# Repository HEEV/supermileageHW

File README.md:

# Cedarville Supermileage HW
Kicad files for PCBs on the Ceaderville Supermileage team. Also includes wiring diagrams and schematics
drawn in Kicad.
#Contents of Folders
* Library Folders
    * EllicottSamuel: Files I made before supermileage which were too much work to port over.
    *  parts_library: Files dedicated for the supermileage team.

* Project Folders
    * can_sensor: PCB to connect generic sensors to the CANBus.
    * current_sensor: Three port current sensor board that connects to the CANBus. 
	Current sensor chip is the Allegro ACS710.
    * pressure_sensor: Pressure sensor board, output as an analog voltage. 
	Supported sensors are the Honeywell ASDX100A24R, Honeywell HSCDRR004MD, and the
	AllSensors G4V-Mini.
    * Sting: wiring diagrams and schematics for Sting produced using Kicad.
        * wiring diagrams: kicad files for the wiring diagrams.
        * schematics: kicad files for the schematics.
    * Urbie: wiring diagrams and schematics for Urbie produced using Kicad.
    	* wiring diagrams: kicad files for the wiring diagrams.
        * schematics: kicad files for the schematics.

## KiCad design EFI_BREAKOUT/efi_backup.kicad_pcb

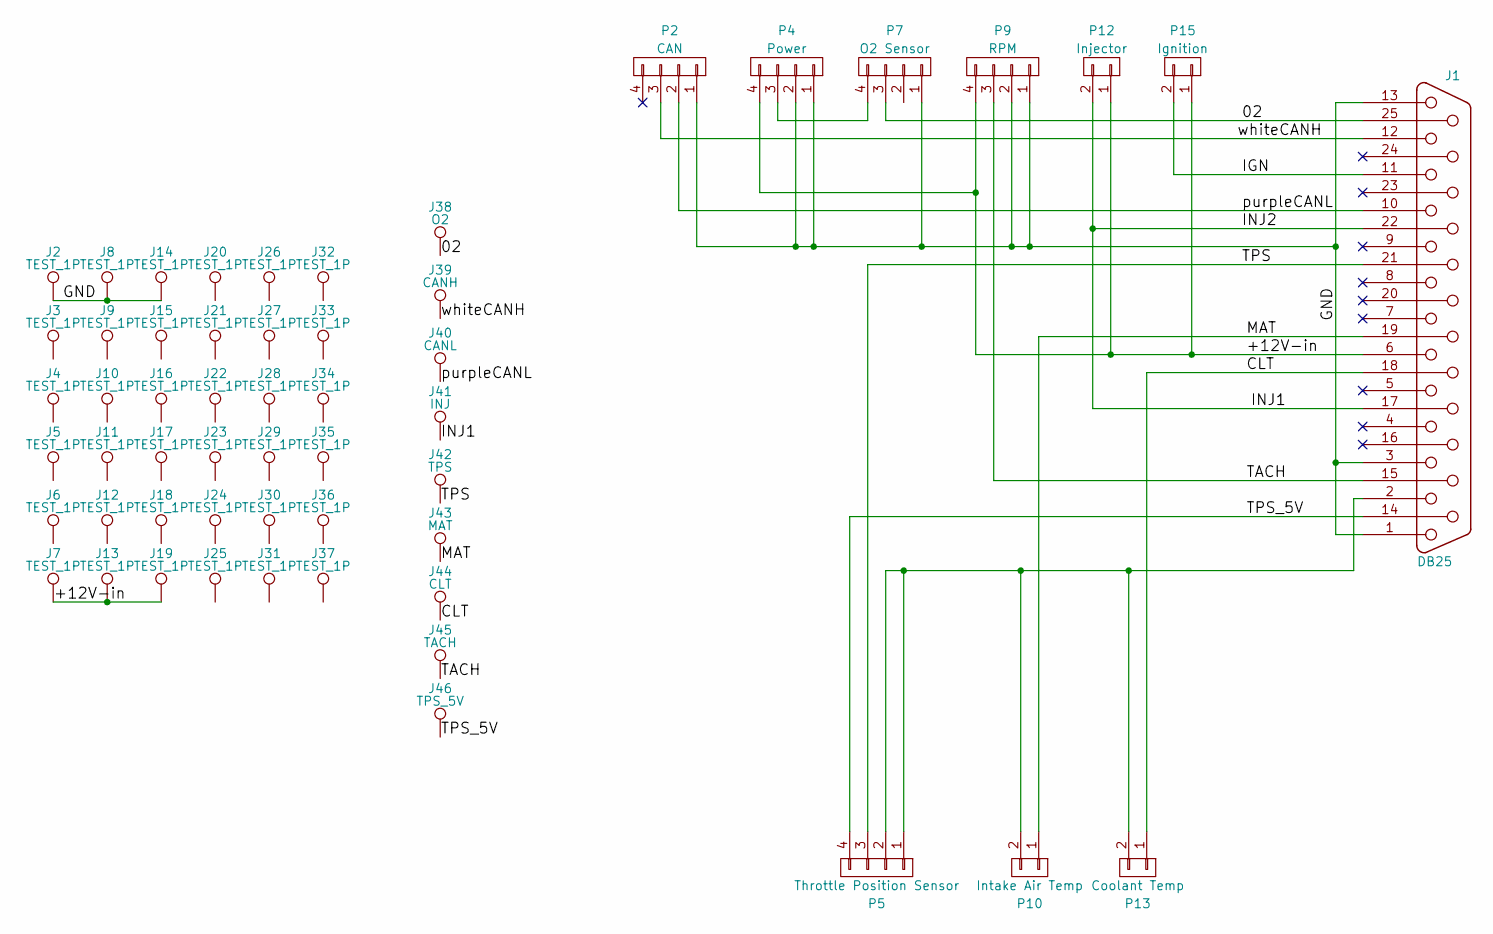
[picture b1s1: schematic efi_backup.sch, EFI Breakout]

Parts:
J1: DB25; DB25F_CI
J2, J3, J4, J5, J6, J7, J8, J9, J10, J11, J12, J13, J14, J15, J16, J17, J18, J19, J20, J21, J22, J23, J24, J25, J26, J27, J28, J29, J30, J31, J32, J33, J34, J35, J36, J37: TEST_1P; Pin_Header_Straight_1x01_Pitch2.54mm
J38: O2; Pin_Header_Straight_1x01_Pitch2.54mm
J39: CANH; Pin_Header_Straight_1x01_Pitch2.54mm
J40: CANL; Pin_Header_Straight_1x01_Pitch2.54mm
J41: INJ; Pin_Header_Straight_1x01_Pitch2.54mm
J42: TPS; Pin_Header_Straight_1x01_Pitch2.54mm
J43: MAT; Pin_Header_Straight_1x01_Pitch2.54mm
J44: CLT; Pin_Header_Straight_1x01_Pitch2.54mm
J45: TACH; Pin_Header_Straight_1x01_Pitch2.54mm
J46: TPS_5V; Pin_Header_Straight_1x01_Pitch2.54mm
P2: CAN; Pin_Header_Straight_1x01_Pitch2.54mm
P4: Power; Molex-UltraFit-4p
P5: Throttle Position Sensor; Molex-UltraFit-4p
P7: O2 Sensor; Molex-UltraFit-4p
P9: RPM; Molex-UltraFit-4p
P10: Intake Air Temp; Molex-UltraFit-2p
P12: Injector; Molex-UltraFit-2p
P13: Coolant Temp; Molex-UltraFit-2p
P15: Ignition; Molex-UltraFit-2p

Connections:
/02: J1.25, J38.1, P7.3
/+12V-in: J1.6, J7.1, J13.1, J19.1, P4.4, P9.4, P12.1, P15.1
/CLT: J1.18, J44.1, P13.1
/GND: J1.1, J1.3, J1.13, J2.1, J8.1, J14.1, P2.1, P4.1, P4.2, P7.1, P9.1, P9.2
/IGN: J1.11, P15.2
/INJ1: J1.17, J1.22, J41.1, P12.2
/MAT: J1.19, J43.1, P10.1
/TACH: J1.15, J45.1, P9.3
/TPS: J1.21, J42.1, P5.3
/TPS_5V: J1.14, J46.1, P5.4
/purpleCANL: J1.10, J40.1, P2.2
/whiteCANH: J1.12, J39.1, P2.3
unnamed: J1.2, P5.1, P5.2, P10.2, P13.2
unnamed: P4.3, P7.4

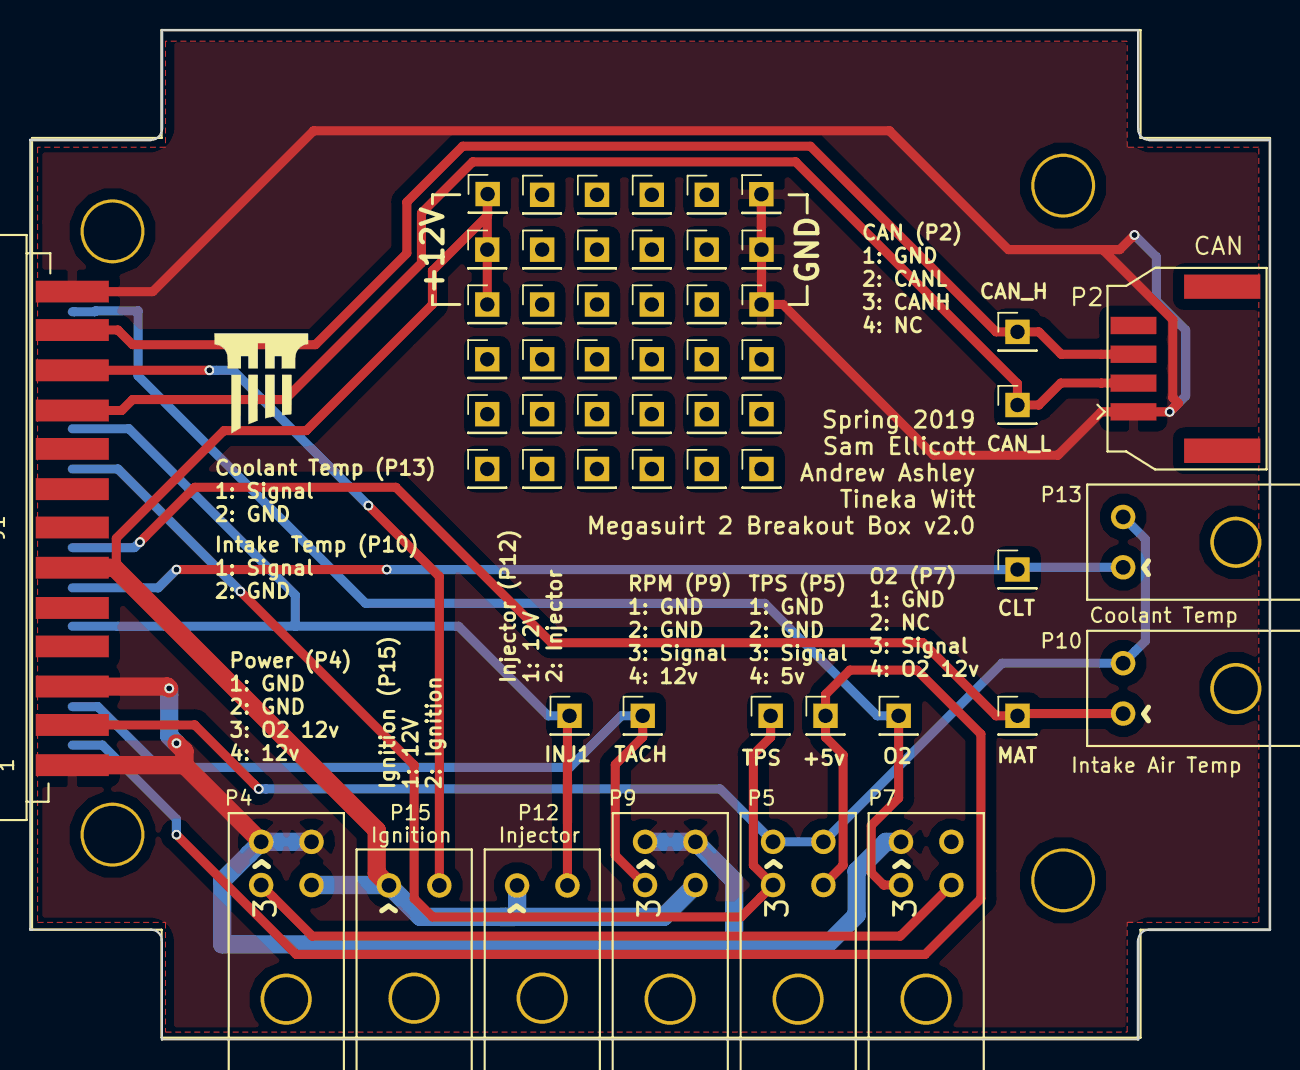
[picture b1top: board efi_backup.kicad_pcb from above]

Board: 2 copper layers, 86.1 x 70.1 mm, 55 parts (0 on the bottom side), 14 nets.

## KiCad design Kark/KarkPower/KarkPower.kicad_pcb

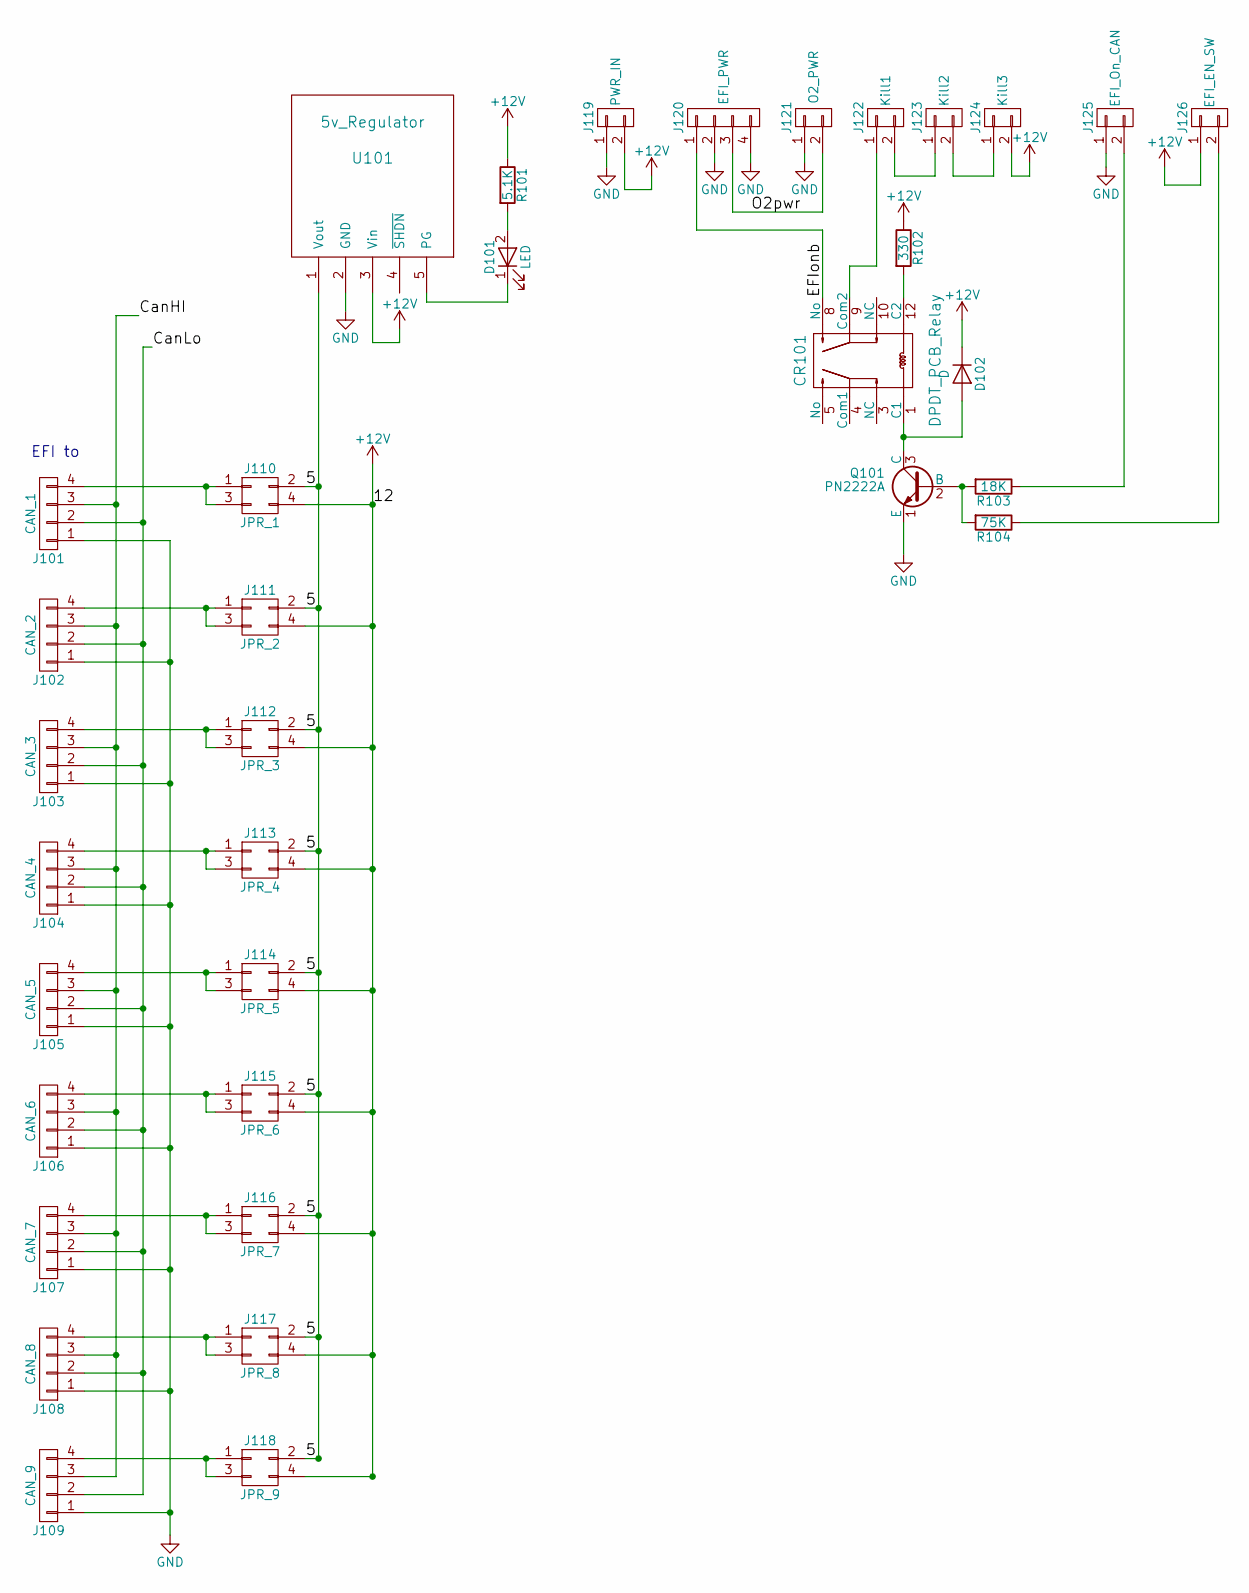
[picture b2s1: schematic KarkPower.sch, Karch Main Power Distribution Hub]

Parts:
CR101: DPDT_PCB_Relay
D101: LED; LED_D3.0mm
D102: D; D_DO-41_SOD81_P7.62mm_Horizontal
J101: CAN_1
J102: CAN_2
J103: CAN_3
J104: CAN_4
J105: CAN_5
J106: CAN_6
J107: CAN_7
J108: CAN_8
J109: CAN_9
J110: JPR_1
J111: JPR_2
J112: JPR_3
J113: JPR_4
J114: JPR_5
J115: JPR_6
J116: JPR_7
J117: JPR_8
J118: JPR_9
J119: PWR_IN
J120: EFI_PWR
J121: O2_PWR
J122: Kill1
J123: Kill2
J124: Kill3
J125: EFI_On_CAN
J126: EFI_EN_SW
Q101: PN2222A; TO-92_Molded_Narrow
R101: 5.1K
R102: 330
R103: 18K
R104: 75K
U101: 5v_Regulator

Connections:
+12V: D102.1 (K), J110.4, J111.4, J112.4, J113.4, J114.4, J115.4, J116.4, J117.4, J118.4, J119.2, J124.2, J126.1, R101.1, R102.1, U101.3 (Vin)
/5: J110.2, J111.2, J112.2, J113.2, J114.2, J115.2, J116.2, J117.2, J118.2, U101.1 (Vout)
/CanHI: J101.3, J102.3, J103.3, J104.3, J105.3, J106.3, J107.3, J108.3, J109.3
/CanLo: J101.2, J102.2, J103.2, J104.2, J105.2, J106.2, J107.2, J108.2, J109.2
/EFIonb: CR101.8 (No), J120.1
/O2pwr: J120.3, J121.2
GND: J101.1, J102.1, J103.1, J104.1, J105.1, J106.1, J107.1, J108.1, J109.1, J119.1, J120.2, J120.4, J121.1, J125.1, Q101.1 (E), U101.2 (GND)
unnamed: CR101.1 (C1), D102.2 (A), Q101.3 (C)
unnamed: CR101.9 (Com2), J122.1
unnamed: CR101.12 (C2), R102.2
unnamed: D101.1 (K), U101.5 (PG)
unnamed: D101.2 (A), R101.2
unnamed: J101.4, J110.1, J110.3
unnamed: J102.4, J111.1, J111.3
unnamed: J103.4, J112.1, J112.3
unnamed: J104.4, J113.1, J113.3
unnamed: J105.4, J114.1, J114.3
unnamed: J106.4, J115.1, J115.3
unnamed: J107.4, J116.1, J116.3
unnamed: J108.4, J117.1, J117.3
unnamed: J109.4, J118.1, J118.3
unnamed: J122.2, J123.1
unnamed: J123.2, J124.1
unnamed: J125.2, R103.1
unnamed: J126.2, R104.1
unnamed: Q101.2 (B), R103.2, R104.2

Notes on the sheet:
EFI to

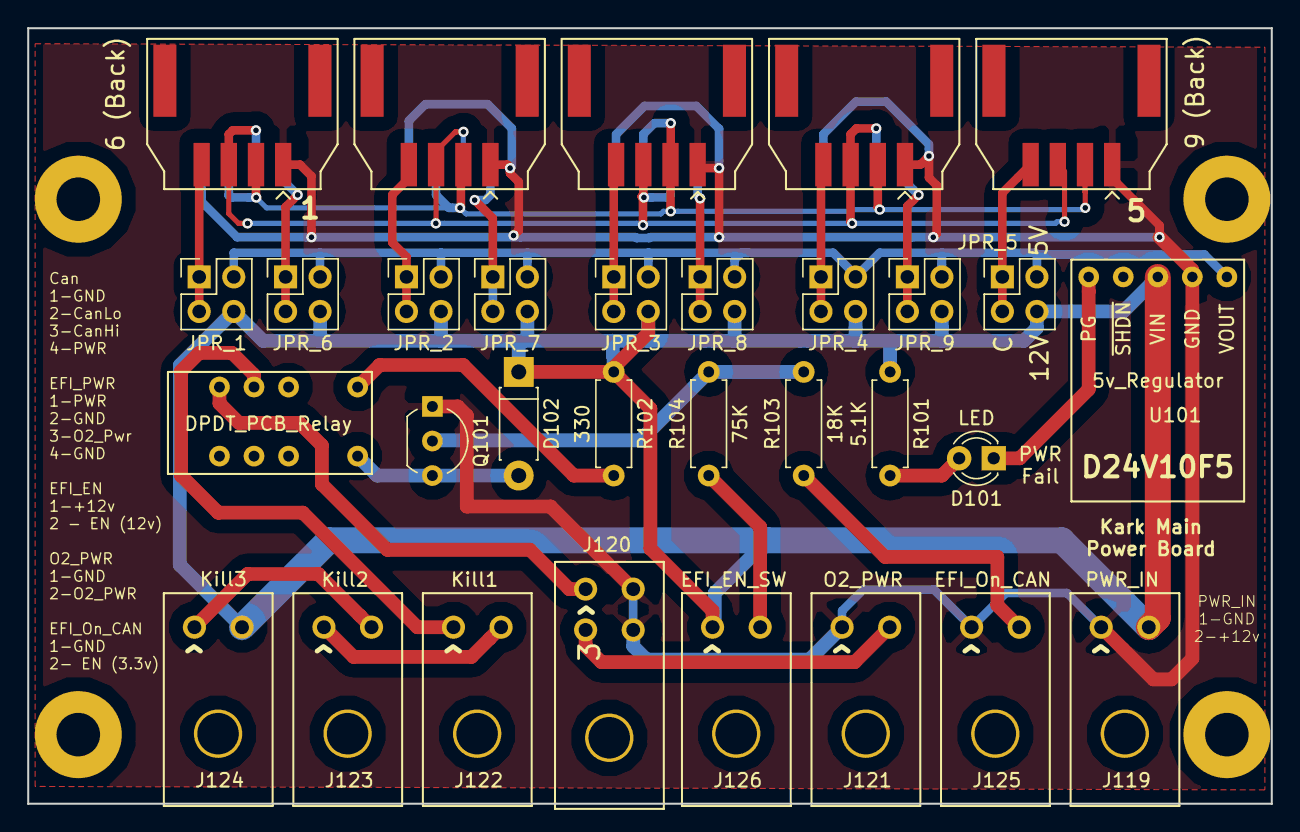
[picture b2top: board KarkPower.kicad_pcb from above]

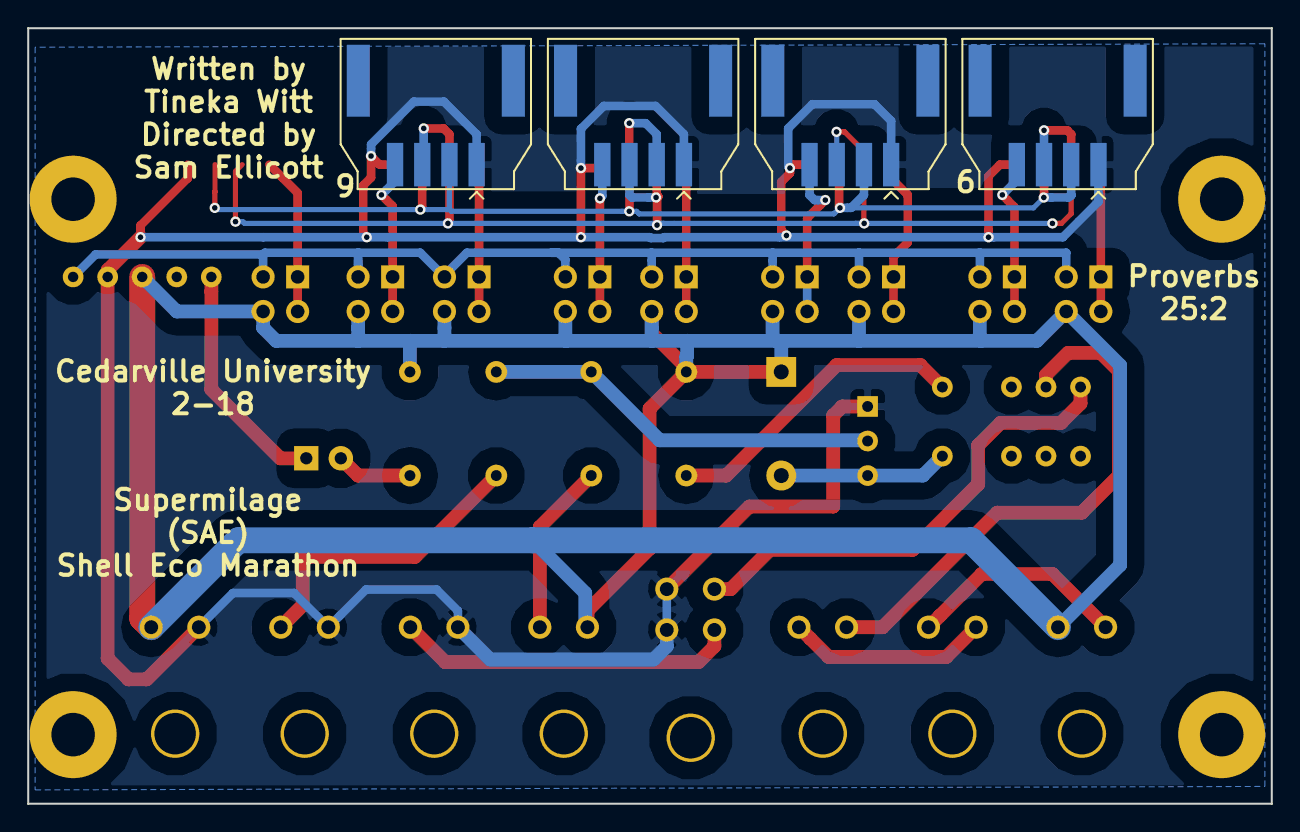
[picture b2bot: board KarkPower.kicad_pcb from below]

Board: 2 copper layers, 91.4 x 57.0 mm, 39 parts (4 on the bottom side), 26 nets.

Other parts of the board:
TP101, TP102, TP103, TP104: TEST; MountingHole_3.2mm_M3_Pad

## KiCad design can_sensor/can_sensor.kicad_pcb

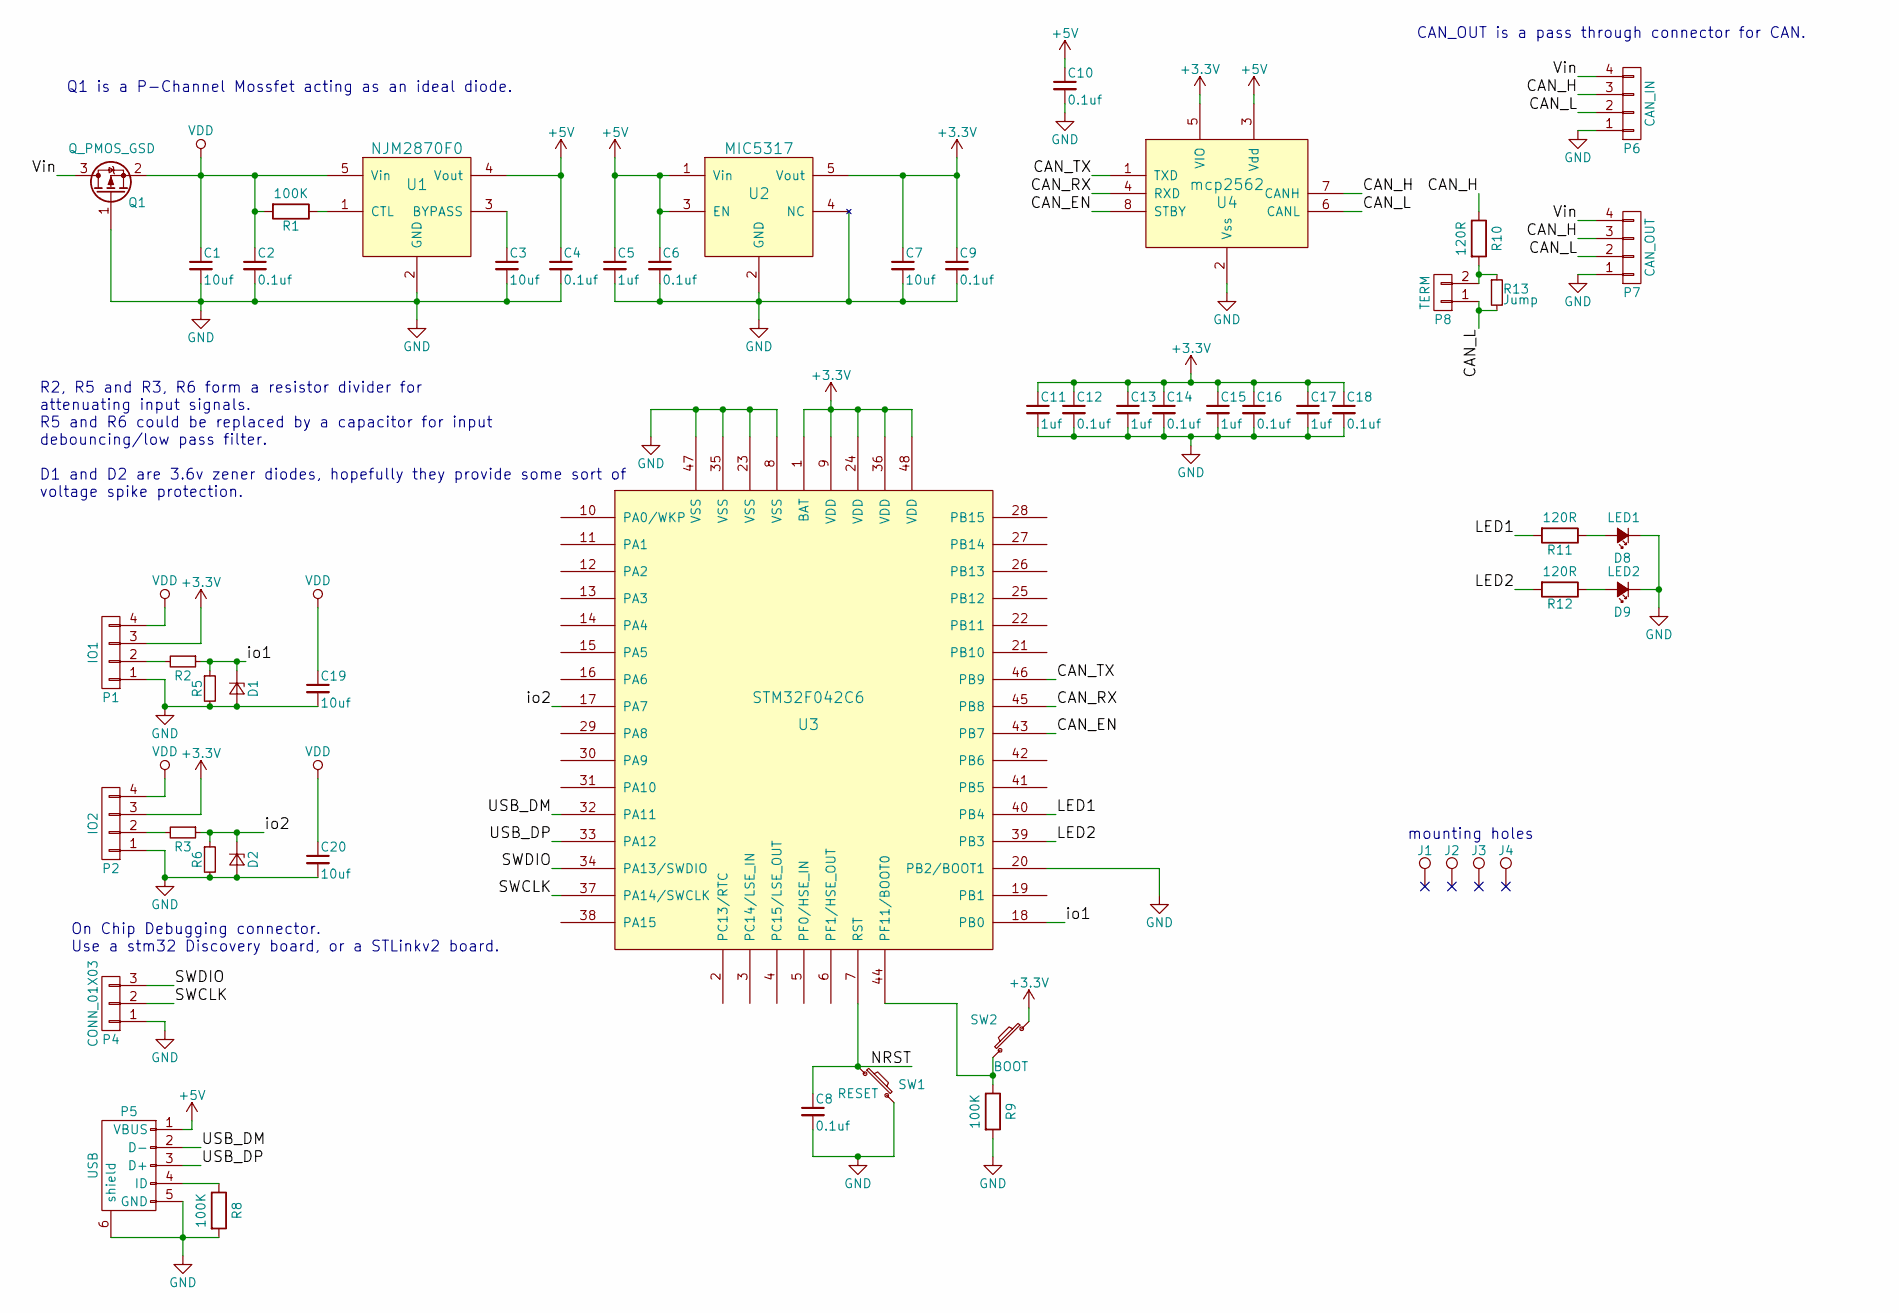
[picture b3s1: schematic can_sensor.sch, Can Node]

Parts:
C1, C3, C7, C19, C20: 10uf; C_0603_HandSoldering
C2, C4, C6, C8, C9, C10, C12, C14, C16, C18: 0.1uf; C_0603_HandSoldering
C5, C11, C13, C15, C17: 1uf; C_0603_HandSoldering
D1, D2: D_Zener_Small; D_SOD-123
D8: LED1; LED_0603
D9: LED2; LED_0603
J1, J2, J3, J4: TEST_1P
P1: IO1; Molex-duraClick-4conn
P2: IO2; Molex-duraClick-4conn
P4: CONN_01X03; Pin_Header_Straight_1x03
P5: USB; USB_Micro-B
P6: CAN_IN; Molex-duraClick-4conn
P7: CAN_OUT; Molex-duraClick-4conn
P8: TERM; Pin_Header_Straight_1x02_Pitch2.54mm
Q1: Q_PMOS_GSD; SOT-23_Handsoldering
R1, R8, R9: 100K; R_0603_HandSoldering
R2, R3, R5, R6: R; R_0603_HandSoldering
R10, R11, R12: 120R; R_0603_HandSoldering
R13: Jump; R_0603
SW1: RESET; SW_SPST_FSMSM
SW2: BOOT; SW_SPST_FSMSM
U1: NJM2870F0; SOT-23-5
U2: MIC5317; SOT-23-5
U3: STM32F042C6; TQFP-48_7x7mm_Pitch0.5mm
U4: mcp2562; SOIC-8-N

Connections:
+3V3: C7.1, C9.1, C11.1, C12.1, C13.1, C14.1, C15.1, C16.1, C17.1, C18.1, P1.3, P2.3, SW2.1, U2.5 (Vout), U3.1 (BAT), U3.9 (VDD), U3.24 (VDD), U3.36 (VDD), U3.48 (VDD), U4.5 (VIO)
+5V: C4.1, C5.1, C6.1, C10.1, P5.1 (VBUS), U1.4 (Vout), U2.1 (Vin), U2.3 (EN), U4.3 (Vdd)
/CAN_EN: U3.43 (PB7), U4.8 (STBY)
/CAN_H: P6.3, P7.3, R10.1, U4.7 (CANH)
/CAN_L: P6.2, P7.2, P8.1, R13.2, U4.6 (CANL)
/CAN_RX: U3.45 (PB8), U4.4 (RXD)
/CAN_TX: U3.46 (PB9), U4.1 (TXD)
/LED1: R11.2, U3.40 (PB4)
/LED2: R12.2, U3.39 (PB3)
/NRST: C8.1, SW1.1, U3.7 (RST)
/SWCLK: P4.2, U3.37 (PA14/SWCLK)
/SWDIO: P4.3, U3.34 (PA13/SWDIO)
/USB_DM: P5.2 (D-), U3.32 (PA11)
/USB_DP: P5.3 (D+), U3.33 (PA12)
/Vin: P6.4, P7.4, Q1.3 (D)
/io1: D1.1 (K), R2.1, R5.1, U3.18 (PB0)
/io2: D2.1 (K), R3.1, R6.1, U3.17 (PA7)
GND: C1.2, C2.2, C3.2, C4.2, C5.2, C6.2, C7.2, C8.2, C9.2, C10.2, C11.2, C12.2, C13.2, C14.2, C15.2, C16.2, C17.2, C18.2, C19.2, C20.2, D1.2 (A), D2.2 (A), D8.1 (K), D9.1 (K), P1.1, P2.1, P4.1, P5.5 (GND), P5.6 (shield), P6.1, P7.1, Q1.1 (G), R5.2, R6.2, R8.2, R9.2, SW1.2, U1.2 (GND), U2.2 (GND), U2.4 (NC), U3.8 (VSS), U3.20 (PB2/BOOT1), U3.23 (VSS), U3.35 (VSS), U3.47 (VSS), U4.2 (Vss)
unnamed: C3.1, U1.3 (BYPASS)
unnamed: D8.2 (A), R11.1
unnamed: D9.2 (A), R12.1
unnamed: P1.2, R2.2
unnamed: P2.2, R3.2
unnamed: P5.4 (ID), R8.1
unnamed: P8.2, R10.2, R13.1
unnamed: R1.1, U1.1 (CTL)
unnamed: R9.1, SW2.2, U3.44 (PF11/BOOT0)
VDD: C1.1, C2.1, C19.1, C20.1, P1.4, P2.4, Q1.2 (S), R1.2, U1.5 (Vin)

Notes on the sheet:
R2, R5 and R3, R6 form a resistor divider for attenuating input signals. R5 and R6 could be replaced by a capacitor for input debouncing/low pass filter. D1 and D2 are 3.6v zener diodes, hopefully they provide some sort of voltage spike protection.
CAN_OUT is a pass through connector for CAN.
On Chip Debugging connector. Use a stm32 Discovery board, or a STLinkv2 board.
Q1 is a P-Channel Mossfet acting as an ideal diode.
mounting holes

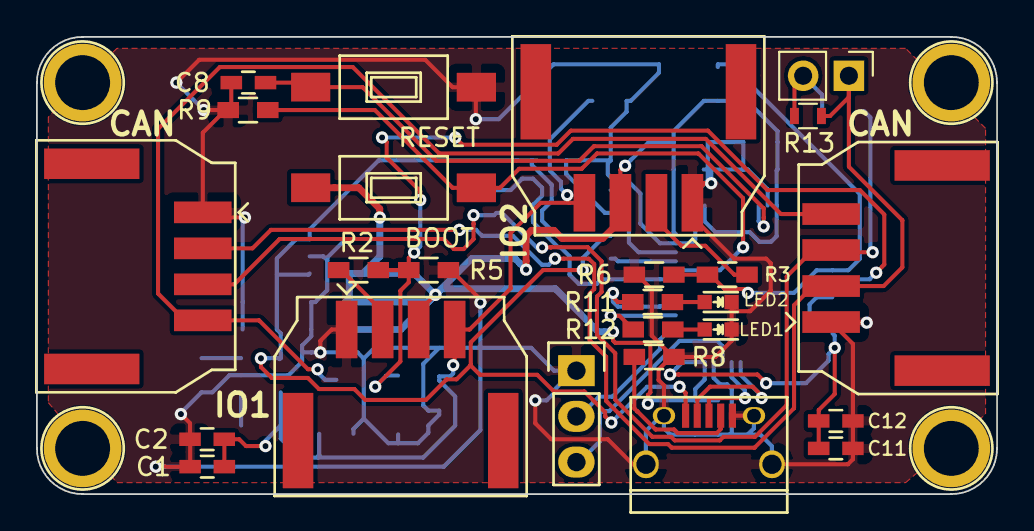
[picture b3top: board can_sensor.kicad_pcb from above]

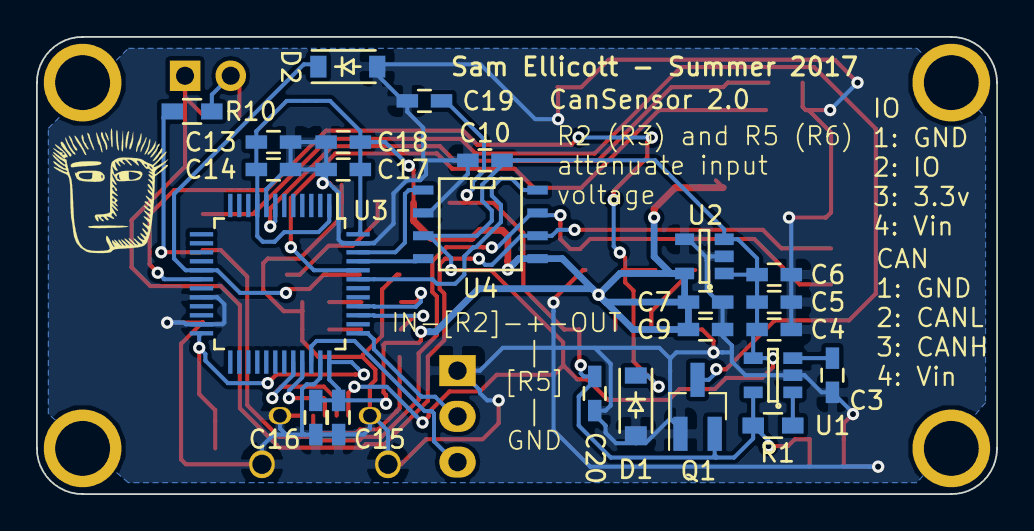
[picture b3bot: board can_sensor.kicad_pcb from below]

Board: 2 copper layers, 53.3 x 25.4 mm, 49 parts (24 on the bottom side), 28 nets.

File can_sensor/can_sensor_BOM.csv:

Reference,Value,Footprint,Count,Datasheet,FootprintLib,Distributor,PN
U4,mcp2562,SOIC-8-N,1,,SMD_Packages,Mouser,579-MCP2562-E/SN
U2,MIC5317,SOT-23-5,1,,TO_SOT_Packages_SMD,Mouser,998-MIC5317-3.3YM5TR
C7;C3;C1;C19;C20,10uf,C_0603_HandSoldering,5,,Capacitors_SMD,Mouser,80-C0603C105K8P
C6;C16;C9;C10;C2;C8;C4;C18;C14;C12,0.1uf,C_0603_HandSoldering,10,,Capacitors_SMD,,
C15;C5;C17;C13;C11,1uf,C_0603_HandSoldering,5,,Capacitors_SMD,Mouser,80-C0603C105K8P
D7,reverse,SOD-123,1,,Diodes_SMD,Mouser,581-SD1206S040S0R5
P6,CAN_IN,Molex-duraClick-4conn,1,,User_Connectors,Mouser,538-53261-0471
P7,CAN_OUT,Molex-duraClick-4conn,1,,User_Connectors,Mouser,538-53261-0471
P1,IO1,Molex-duraClick-4conn,1,,User_Connectors,Mouser,538-53261-0471
P2,IO2,Molex-duraClick-4conn,1,,User_Connectors,Mouser,538-53261-0471
R10;R11;R12,120R,R_0603_HandSoldering,3,,Resistors_SMD,Mouser,71-CRCW0603-120-E3
D8,LED1,LED_0603,1,,LEDs,,
D9,LED2,LED_0603,1,,LEDs,,
P5,USB,USB_Micro-B,1,,Connect,Mouser,649-10118194-0001LF
SW2,BOOT,SW_SPST_FSMSM,1,,Buttons_Switches_SMD,,
SW1,RESET,SW_SPST_FSMSM,1,,Buttons_Switches_SMD,,
U1,NJM2870F0,SOT-23-5,1,,TO_SOT_Packages_SMD,Mouser,513-NJM2870F05-TE2
R1;R9;R8,100K,R_0603_HandSoldering,3,,Resistors_SMD,Mouser,71-CRCW0603-100K-E3
P4,CONN_01X03,Pin_Header_Straight_1x03,1,,Pin_Headers,,
D1;D2;D3;D4,hi_v,SOD-123,4,,Diodes_SMD,,
R6;R5;R3;R2,R,R_0603_HandSoldering,4,,Resistors_SMD,,
U3,STM32F042C6,TQFP-48_7x7mm_Pitch0.5mm,1,,Housings_QFP,,

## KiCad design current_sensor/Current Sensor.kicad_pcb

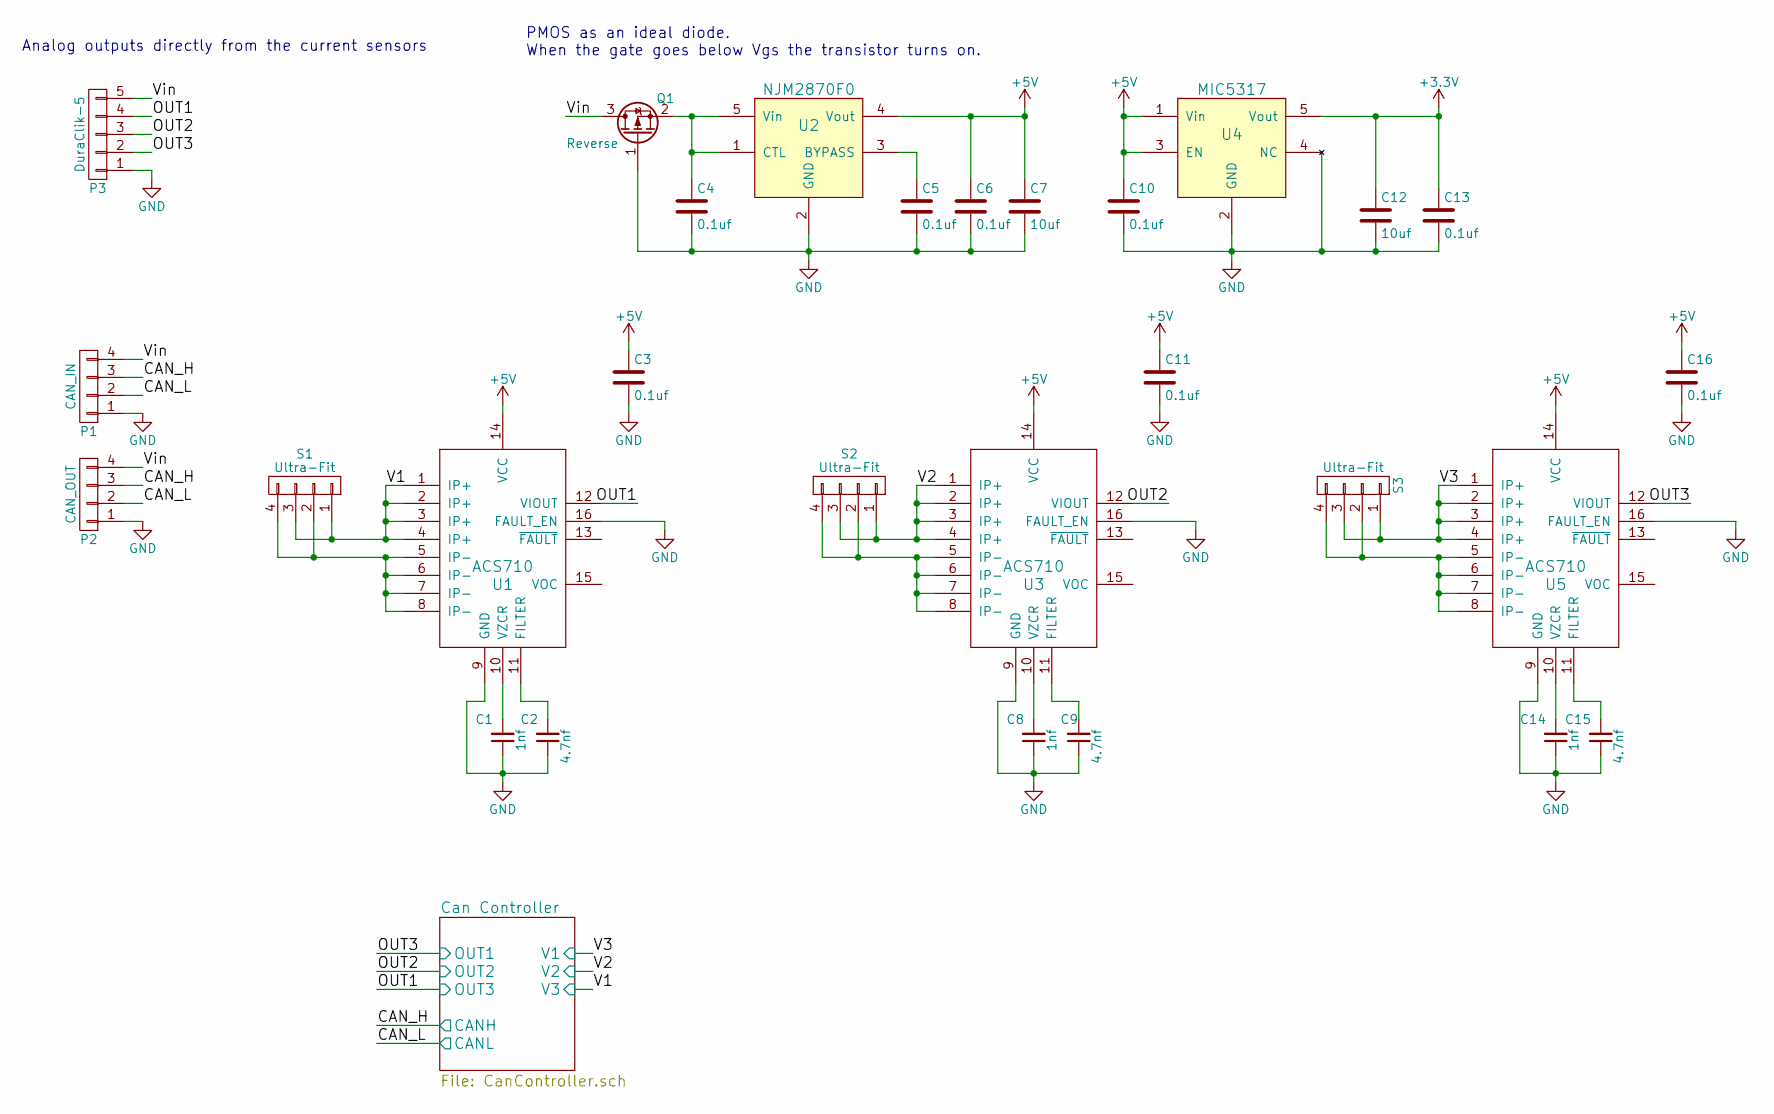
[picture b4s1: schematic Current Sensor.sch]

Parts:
C1, C8, C14: 1nf; C_0603_HandSoldering
C2, C9, C15: 4.7nf; C_0603_HandSoldering
C3, C4, C5, C6, C10, C11, C13, C16: 0.1uf; C_0603_HandSoldering
C7, C12: 10uf; C_0603_HandSoldering
P1: CAN_IN; Molex-duraClick-4conn
P2: CAN_OUT; Molex-duraClick-4conn
P3: DuraClik-5; Molex-duraClick-5conn
Q1: Reverse; SOT-23_Handsoldering
S1, S2, S3: Ultra-Fit; Molex-UltraFit-4p
U1, U3, U5: ACS710; DIP-16-SchmartBoard
U2: NJM2870F0; SOT-23-5
U4: MIC5317; SOT-23-5

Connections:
+3V3: C12.1, C13.1, U4.5 (Vout); also elsewhere on the board
+5V: C3.1, C6.1, C7.1, C10.1, C11.1, C16.1, U1.14 (VCC), U2.4 (Vout), U3.14 (VCC), U4.1 (Vin), U4.3 (EN), U5.14 (VCC); also elsewhere on the board
/CAN_H: P1.3, P2.3; also elsewhere on the board
/CAN_L: P1.2, P2.2; also elsewhere on the board
/OUT1: P3.4, U1.12 (VIOUT); also elsewhere on the board
/OUT2: P3.3, U3.12 (VIOUT); also elsewhere on the board
/OUT3: P3.2, U5.12 (VIOUT); also elsewhere on the board
/V1: S1.1, S1.3, U1.1 (IP+), U1.2 (IP+), U1.3 (IP+), U1.4 (IP+); also elsewhere on the board
/V2: S2.1, S2.3, U3.1 (IP+), U3.2 (IP+), U3.3 (IP+), U3.4 (IP+); also elsewhere on the board
/V3: S3.1, S3.3, U5.1 (IP+), U5.2 (IP+), U5.3 (IP+), U5.4 (IP+); also elsewhere on the board
/Vin: P1.4, P2.4, P3.5, Q1.3 (D)
GND: C1.1, C2.1, C3.2, C4.2, C5.2, C6.2, C7.2, C8.1, C9.1, C10.2, C11.2, C12.2, C13.2, C14.1, C15.1, C16.2, P1.1, P2.1, P3.1, Q1.1 (G), U1.9 (GND), U1.16 (FAULT_EN), U2.2 (GND), U3.9 (GND), U3.16 (FAULT_EN), U4.2 (GND), U4.4 (NC), U5.9 (GND), U5.16 (FAULT_EN); also elsewhere on the board
unnamed: C1.2, U1.10 (VZCR)
unnamed: C2.2, U1.11 (FILTER)
unnamed: C4.1, Q1.2 (S), U2.1 (CTL), U2.5 (Vin)
unnamed: C5.1, U2.3 (BYPASS)
unnamed: C8.2, U3.10 (VZCR)
unnamed: C9.2, U3.11 (FILTER)
unnamed: C14.2, U5.10 (VZCR)
unnamed: C15.2, U5.11 (FILTER)
unnamed: S1.2, S1.4, U1.5 (IP-), U1.6 (IP-), U1.7 (IP-), U1.8 (IP-)
unnamed: S2.2, S2.4, U3.5 (IP-), U3.6 (IP-), U3.7 (IP-), U3.8 (IP-)
unnamed: S3.2, S3.4, U5.5 (IP-), U5.6 (IP-), U5.7 (IP-), U5.8 (IP-)

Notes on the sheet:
Analog outputs directly from the current sensors
PMOS as an ideal diode. When the gate goes below Vgs the transistor turns on.

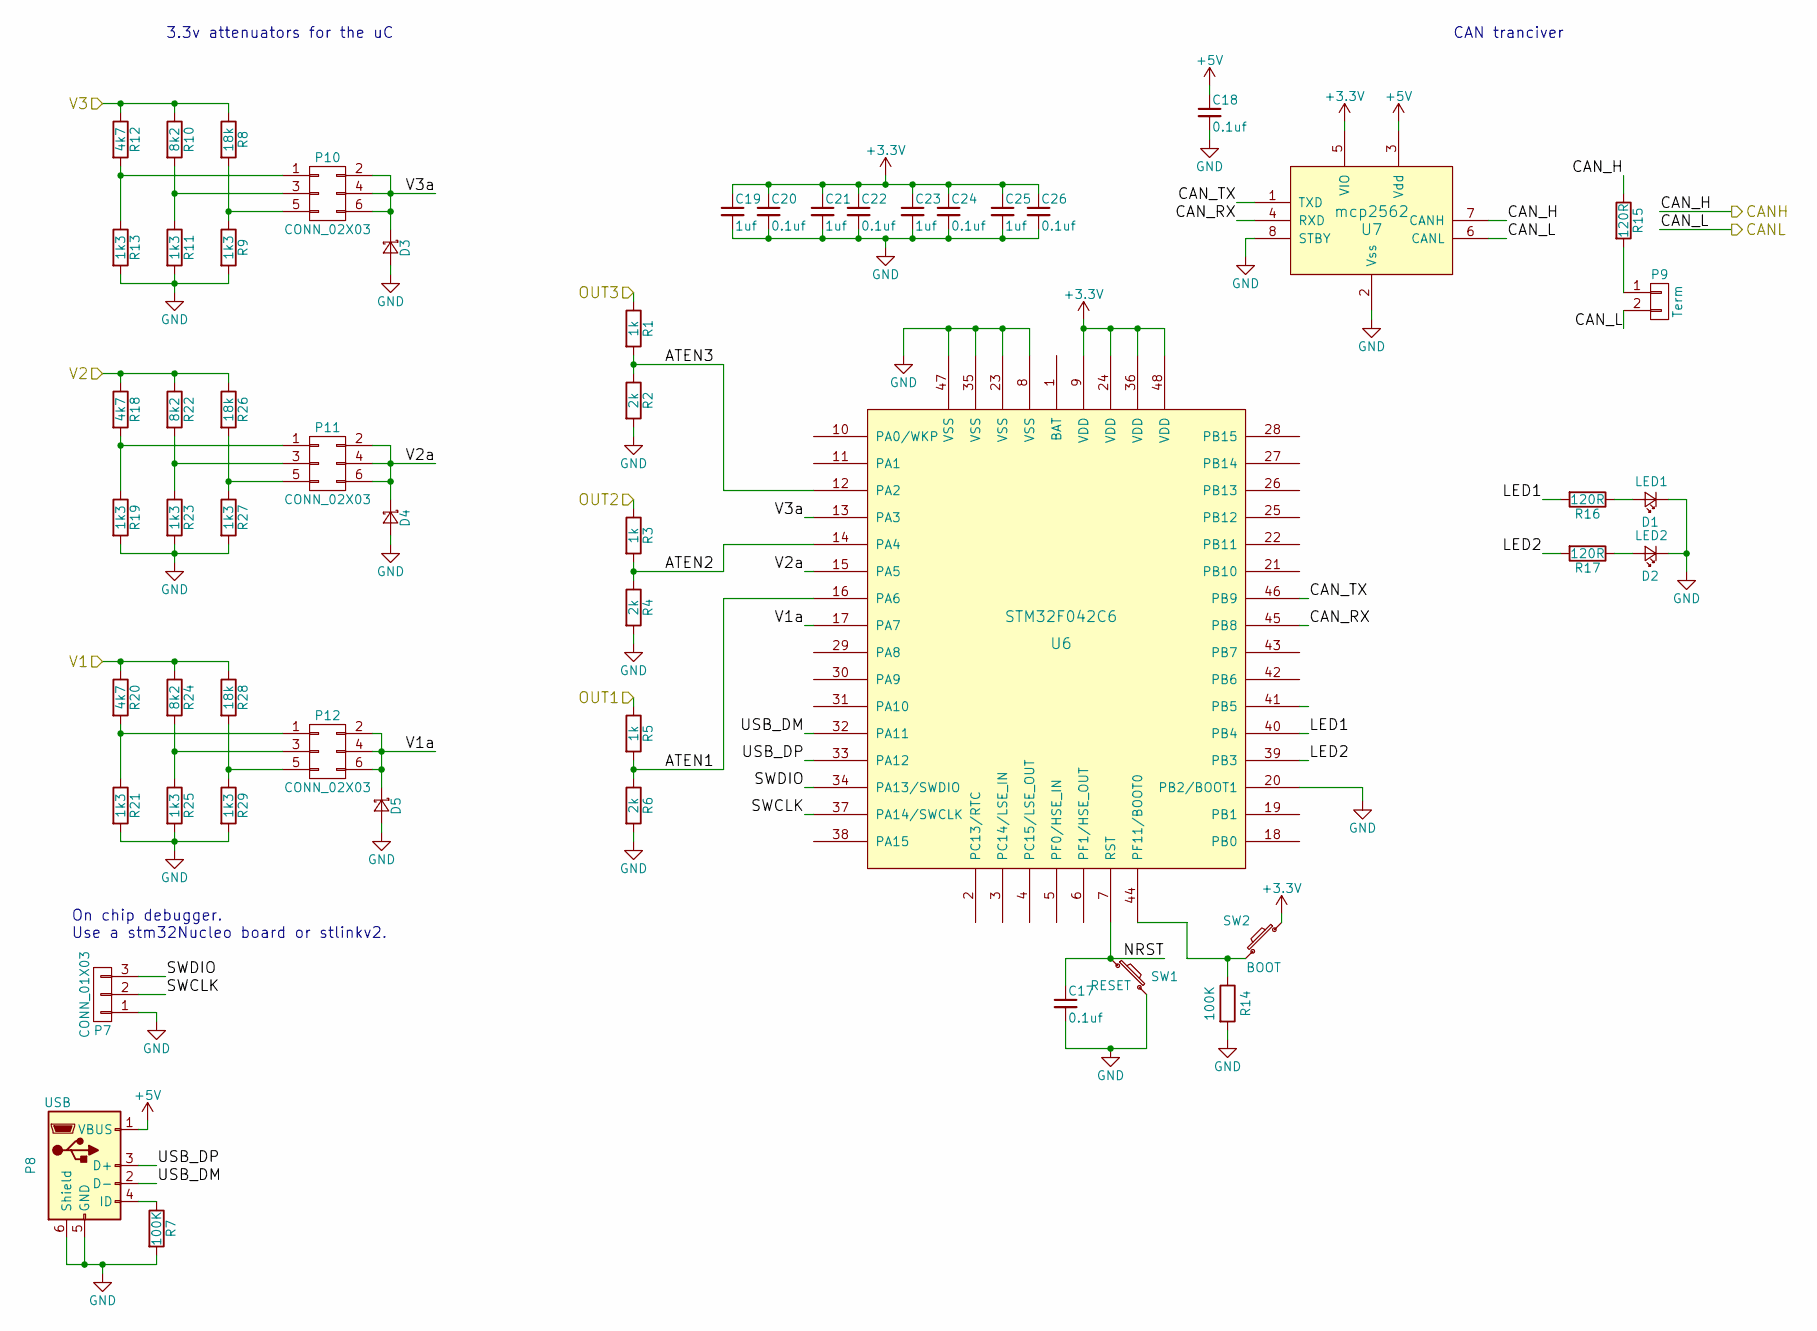
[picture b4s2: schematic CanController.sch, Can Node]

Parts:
C17, C18, C20, C22, C24, C26: 0.1uf; C_0603_HandSoldering
C19, C21, C23, C25: 1uf; C_0603_HandSoldering
D1: LED1; LED-3MM
D2: LED2; LED-3MM
D3, D4, D5: D_Schottky_Small; SOD-123
P7: CONN_01X03; Pin_Header_Straight_1x03
P8: USB; USB_Micro-B
P9: Term; Pin_Header_Straight_1x02
P10, P11, P12: CONN_02X03; Pin_Header_Straight_2x03
R1, R3, R5: 1k; R_0603_HandSoldering
R2, R4, R6: 2k; R_0603_HandSoldering
R7, R14: 100K; R_0603_HandSoldering
R8, R26, R28: 18k; R_0603_HandSoldering
R9, R11, R13, R19, R21, R23, R25, R27, R29: 1k3; R_0603_HandSoldering
R10, R22, R24: 8k2; R_0603_HandSoldering
R12, R18, R20: 4k7; R_0603_HandSoldering
R15, R16, R17: 120R; R_0603_HandSoldering
SW1: RESET; SW_PUSH_6mm
SW2: BOOT; SW_PUSH_6mm
U6: STM32F042C6; TQFP-48_7x7mm_Pitch0.5mm
U7: mcp2562; SOIC-8-N

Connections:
+3V3: C19.1, C20.1, C21.1, C22.1, C23.1, C24.1, C25.1, C26.1, SW2.1, U6.9 (VDD), U6.24 (VDD), U6.36 (VDD), U6.48 (VDD), U7.5 (VIO); also elsewhere on the board
+5V: C18.1, P8.1 (VBUS), U7.3 (Vdd); also elsewhere on the board
/CAN_H: R15.1, U7.7 (CANH); also elsewhere on the board
/CAN_L: P9.2, U7.6 (CANL); also elsewhere on the board
/Can Controller/ATEN1: R5.2, R6.1, U6.16 (PA6)
/Can Controller/ATEN2: R3.2, R4.1, U6.14 (PA4)
/Can Controller/ATEN3: R1.2, R2.1, U6.12 (PA2)
/Can Controller/CAN_RX: U6.45 (PB8), U7.4 (RXD)
/Can Controller/CAN_TX: U6.46 (PB9), U7.1 (TXD)
/Can Controller/LED1: R16.2, U6.40 (PB4)
/Can Controller/LED2: R17.2, U6.39 (PB3)
/Can Controller/NRST: C17.1, SW1.1, U6.7 (RST)
/Can Controller/SWCLK: P7.2, U6.37 (PA14/SWCLK)
/Can Controller/SWDIO: P7.3, U6.34 (PA13/SWDIO)
/Can Controller/USB_DM: P8.2 (D-), U6.32 (PA11)
/Can Controller/USB_DP: P8.3 (D+), U6.33 (PA12)
/Can Controller/V1a: D5.1 (K), P12.2, P12.4, P12.6, U6.17 (PA7)
/Can Controller/V2a: D4.1 (K), P11.2, P11.4, P11.6, U6.15 (PA5)
/Can Controller/V3a: D3.1 (K), P10.2, P10.4, P10.6, U6.13 (PA3)
/OUT1: R1.1; also elsewhere on the board
/OUT2: R3.1; also elsewhere on the board
/OUT3: R5.1; also elsewhere on the board
/V1: R8.1, R10.1, R12.1; also elsewhere on the board
/V2: R18.1, R22.1, R26.1; also elsewhere on the board
/V3: R20.1, R24.1, R28.1; also elsewhere on the board
GND: C17.2, C18.2, C19.2, C20.2, C21.2, C22.2, C23.2, C24.2, C25.2, C26.2, D1.1 (K), D2.1 (K), D3.2 (A), D4.2 (A), D5.2 (A), P7.1, P8.5 (GND), P8.6 (Shield), R2.2, R4.2, R6.2, R7.2, R9.2, R11.2, R13.2, R14.2, R19.2, R21.2, R23.2, R25.2, R27.2, R29.2, SW1.2, U6.8 (VSS), U6.20 (PB2/BOOT1), U6.23 (VSS), U6.35 (VSS), U6.47 (VSS), U7.2 (Vss), U7.8 (STBY); also elsewhere on the board
unnamed: D1.2 (A), R16.1
unnamed: D2.2 (A), R17.1
unnamed: P8.4 (ID), R7.1
unnamed: P9.1, R15.2
unnamed: P10.1, R12.2, R13.1
unnamed: P10.3, R10.2, R11.1
unnamed: P10.5, R8.2, R9.1
unnamed: P11.1, R18.2, R19.1
unnamed: P11.3, R22.2, R23.1
unnamed: P11.5, R26.2, R27.1
unnamed: P12.1, R20.2, R21.1
unnamed: P12.3, R24.2, R25.1
unnamed: P12.5, R28.2, R29.1
unnamed: R14.1, SW2.2, U6.44 (PF11/BOOT0)

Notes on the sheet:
3.3v attenuators for the uC
CAN tranciver
On chip debugger. Use a stm32Nucleo board or stlinkv2.
